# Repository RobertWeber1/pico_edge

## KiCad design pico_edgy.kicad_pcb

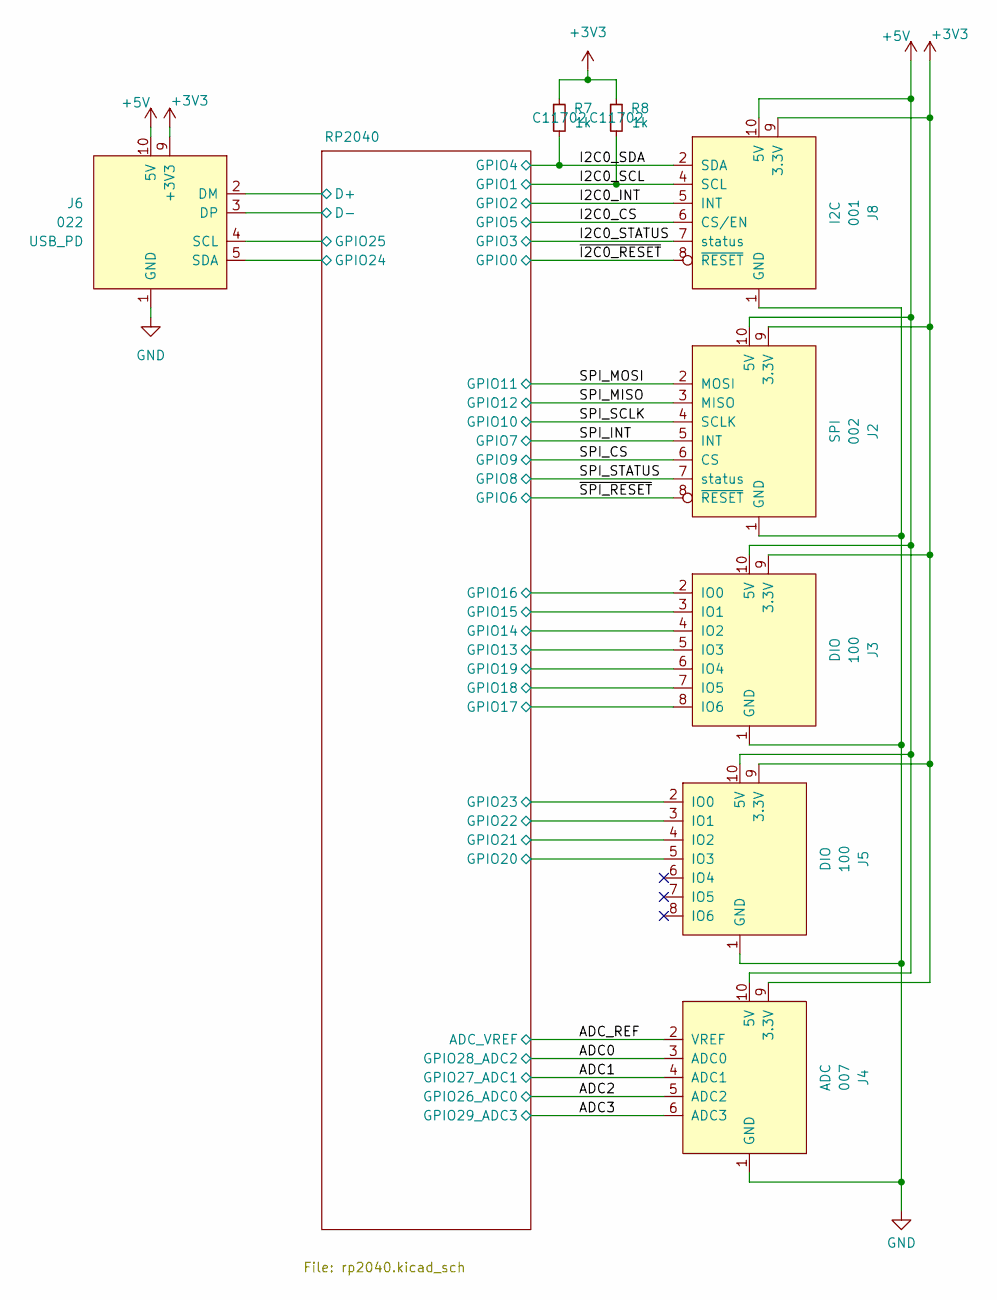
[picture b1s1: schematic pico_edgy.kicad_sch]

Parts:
J2: 002; on_edge_2x05_host
J3, J5: 100; on_edge_2x05_host
J4: 007; on_edge_2x05_host
J6: 022; on_edge_2x05_host
J8: 001; on_edge_2x05_host
R7, R8: 1k; R_0402_1005Metric; LCSC C25543

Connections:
+3V3: J2.9 (3.3V), J3.9 (3.3V), J4.9 (3.3V), J5.9 (3.3V), J6.9 (+3V3), J8.9 (3.3V), R7.1, R8.1; also elsewhere on the board
+5V: J2.10 (5V), J3.10 (5V), J4.10 (5V), J5.10 (5V), J6.10 (5V), J8.10 (5V)
/ADC0: J4.3 (ADC0); also elsewhere on the board
/ADC1: J4.4 (ADC1); also elsewhere on the board
/ADC2: J4.5 (ADC2); also elsewhere on the board
/ADC3: J4.6 (ADC3); also elsewhere on the board
/ADC_REF: J4.2 (VREF); also elsewhere on the board
/I2C0_CS: J8.6 (CS/EN); also elsewhere on the board
/I2C0_INT: J8.5 (INT); also elsewhere on the board
/I2C0_SCL: J8.4 (SCL), R8.2; also elsewhere on the board
/I2C0_SDA: J8.2 (SDA), R7.2; also elsewhere on the board
/I2C0_STATUS: J8.7 (status); also elsewhere on the board
/RP2040/D+: J6.2 (DM); also elsewhere on the board
/RP2040/D-: J6.3 (DP); also elsewhere on the board
/RP2040/GPIO13: J3.5 (IO3); also elsewhere on the board
/RP2040/GPIO14: J3.4 (IO2); also elsewhere on the board
/RP2040/GPIO15: J3.3 (IO1); also elsewhere on the board
/RP2040/GPIO16: J3.2 (IO0); also elsewhere on the board
/RP2040/GPIO17: J3.8 (IO6); also elsewhere on the board
/RP2040/GPIO18: J3.7 (IO5); also elsewhere on the board
/RP2040/GPIO19: J3.6 (IO4); also elsewhere on the board
/RP2040/GPIO20: J5.5 (IO3); also elsewhere on the board
/RP2040/GPIO21: J5.4 (IO2); also elsewhere on the board
/RP2040/GPIO22: J5.3 (IO1); also elsewhere on the board
/RP2040/GPIO23: J5.2 (IO0); also elsewhere on the board
/RP2040/GPIO24: J6.5 (SDA); also elsewhere on the board
/RP2040/GPIO25: J6.4 (SCL); also elsewhere on the board
/SPI_CS: J2.6 (CS); also elsewhere on the board
/SPI_INT: J2.5 (INT); also elsewhere on the board
/SPI_MISO: J2.3 (MISO); also elsewhere on the board
/SPI_MOSI: J2.2 (MOSI); also elsewhere on the board
/SPI_SCLK: J2.4 (SCLK); also elsewhere on the board
/SPI_STATUS: J2.7 (status); also elsewhere on the board
/~I2C0_RESET: J8.8 (~RESET); also elsewhere on the board
/~SPI_RESET: J2.8 (~RESET); also elsewhere on the board
GND: J2.1 (GND), J3.1 (GND), J4.1 (GND), J5.1 (GND), J6.1 (GND), J8.1 (GND); also elsewhere on the board

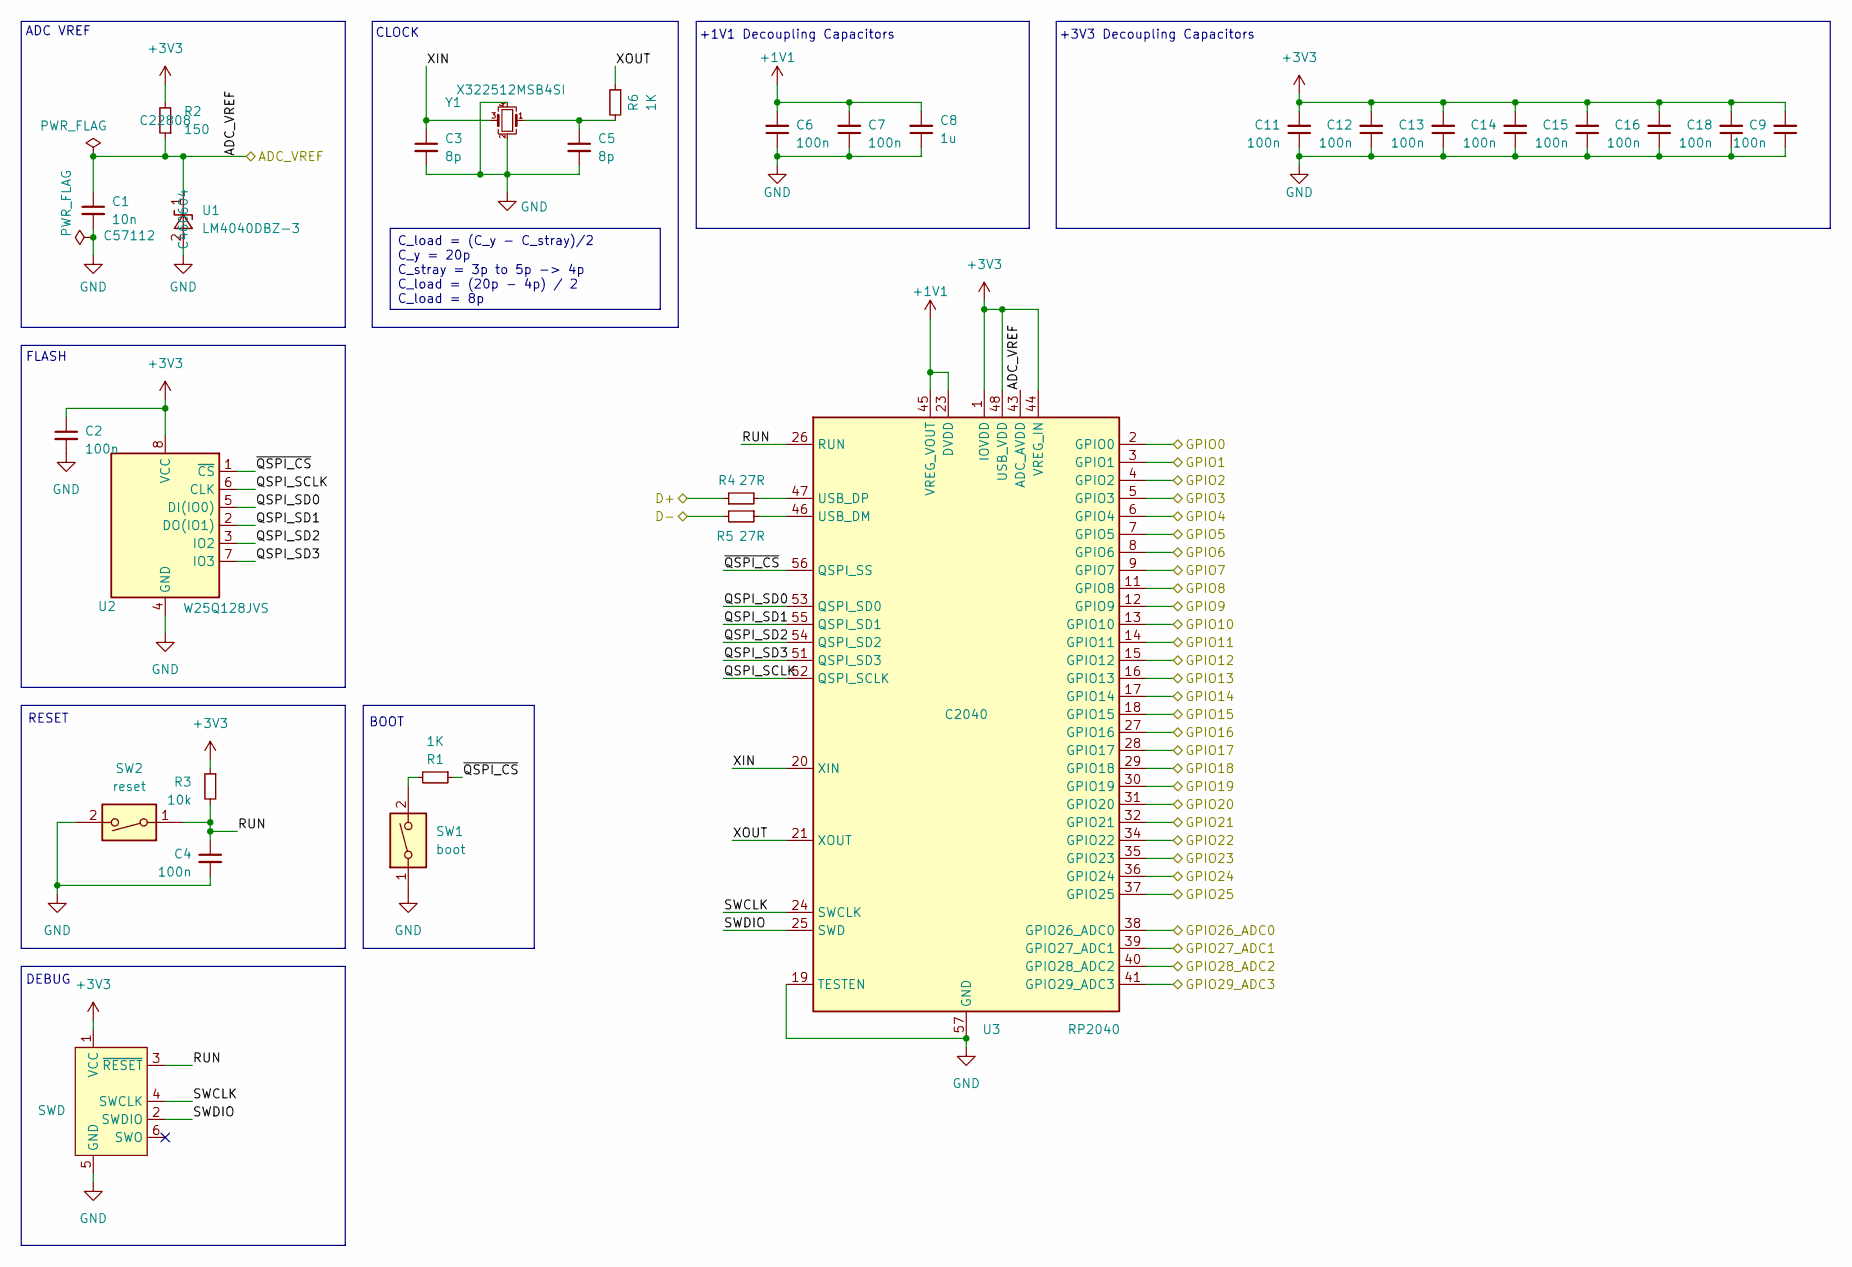
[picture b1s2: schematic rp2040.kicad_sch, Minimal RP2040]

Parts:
C1: 10n; C_0603_1608Metric_Pad1.08x0.95mm_HandSolder; LCSC C76599
C2, C4, C6, C7, C9, C11, C12, C13, C14, C15, C16, C18: 100n; C_0402_1005Metric_Pad0.74x0.62mm_HandSolder; LCSC Part# C307331
C3, C5: 8p; C_0402_1005Metric_Pad0.74x0.62mm_HandSolder; LCSC Part# C130118
C8: 1u; C_0402_1005Metric_Pad0.74x0.62mm_HandSolder; LCSC Part# C52923
J1: SWD; Tag-Connect_TC2030-IDC-NL_2x03_P1.27mm_Vertical
R1, R6: 1K; R_0402_1005Metric_Pad0.72x0.64mm_HandSolder; LCSC Part# C11702
R2: 150; R_0603_1608Metric_Pad0.98x0.95mm_HandSolder; LCSC C22808
R3: 10k; R_0402_1005Metric_Pad0.72x0.64mm_HandSolder; LCSC Part# C25744
R4, R5: 27R; R_0402_1005Metric_Pad0.72x0.64mm_HandSolder; LCSC Part# C140174
SW1: boot; SW_Push_1P1T_XKB_TS-1187A; LCSC Part# C318884
SW2: reset; SW_Push_1P1T_XKB_TS-1187A; LCSC Part# C318884
U1: LM4040DBZ-3; SOT-23; LCSC C460726
U2: W25Q128JVS; WSON-8-1EP_6x5mm_P1.27mm_EP3.4x4.3mm; LCSC Part# C190862
U3: RP2040; QFN-56-1EP_7x7mm_P0.4mm_EP3.2x3.2mm; LCSC Part# C2040
Y1: X322512MSB4SI; Crystal_SMD_3225-4Pin_3.2x2.5mm; LCSC Part# C9002

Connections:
+1V1: C6.2, C7.2, C8.2, U3.23 (DVDD), U3.45 (VREG_VOUT), U3.50 (DVDD)
+3V3: C2.1, C9.2, C11.2, C12.2, C13.2, C14.2, C15.2, C16.2, C18.2, J1.1 (VCC), R2.2, R3.1, U2.8 (VCC), U3.1 (IOVDD), U3.10 (IOVDD), U3.22 (IOVDD), U3.33 (IOVDD), U3.42 (IOVDD), U3.44 (VREG_IN), U3.48 (USB_VDD), U3.49 (IOVDD); also elsewhere on the board
/ADC0: U3.40 (GPIO28_ADC2); also elsewhere on the board
/ADC1: U3.39 (GPIO27_ADC1); also elsewhere on the board
/ADC2: U3.38 (GPIO26_ADC0); also elsewhere on the board
/ADC3: U3.41 (GPIO29_ADC3); also elsewhere on the board
/ADC_REF: C1.1, R2.1, U1.1 (K), U3.43 (ADC_AVDD); also elsewhere on the board
/I2C0_CS: U3.7 (GPIO5); also elsewhere on the board
/I2C0_INT: U3.4 (GPIO2); also elsewhere on the board
/I2C0_SCL: U3.3 (GPIO1); also elsewhere on the board
/I2C0_SDA: U3.6 (GPIO4); also elsewhere on the board
/I2C0_STATUS: U3.5 (GPIO3); also elsewhere on the board
/RP2040/D+: R4.1; also elsewhere on the board
/RP2040/D-: R5.2; also elsewhere on the board
/RP2040/GPIO13: U3.16 (GPIO13); also elsewhere on the board
/RP2040/GPIO14: U3.17 (GPIO14); also elsewhere on the board
/RP2040/GPIO15: U3.18 (GPIO15); also elsewhere on the board
/RP2040/GPIO16: U3.27 (GPIO16); also elsewhere on the board
/RP2040/GPIO17: U3.28 (GPIO17); also elsewhere on the board
/RP2040/GPIO18: U3.29 (GPIO18); also elsewhere on the board
/RP2040/GPIO19: U3.30 (GPIO19); also elsewhere on the board
/RP2040/GPIO20: U3.31 (GPIO20); also elsewhere on the board
/RP2040/GPIO21: U3.32 (GPIO21); also elsewhere on the board
/RP2040/GPIO22: U3.34 (GPIO22); also elsewhere on the board
/RP2040/GPIO23: U3.35 (GPIO23); also elsewhere on the board
/RP2040/GPIO24: U3.36 (GPIO24); also elsewhere on the board
/RP2040/GPIO25: U3.37 (GPIO25); also elsewhere on the board
/RP2040/QSPI_SCLK: U2.6 (CLK), U3.52 (QSPI_SCLK)
/RP2040/QSPI_SD0: U2.5 (DI(IO0)), U3.53 (QSPI_SD0)
/RP2040/QSPI_SD1: U2.2 (DO(IO1)), U3.55 (QSPI_SD1)
/RP2040/QSPI_SD2: U2.3 (IO2), U3.54 (QSPI_SD2)
/RP2040/QSPI_SD3: U2.7 (IO3), U3.51 (QSPI_SD3)
/RP2040/RUN: C4.1, J1.3 (~RESET), R3.2, SW2.1, U3.26 (RUN)
/RP2040/SWCLK: J1.4 (SWCLK), U3.24 (SWCLK)
/RP2040/SWDIO: J1.2 (SWDIO), U3.25 (SWD)
/RP2040/XIN: C3.1, U3.20 (XIN), Y1.3
/RP2040/XOUT: R6.1, U3.21 (XOUT)
/RP2040/~QSPI_CS: R1.1, U2.1 (~CS), U3.56 (QSPI_SS)
/SPI_CS: U3.12 (GPIO9); also elsewhere on the board
/SPI_INT: U3.9 (GPIO7); also elsewhere on the board
/SPI_MISO: U3.15 (GPIO12); also elsewhere on the board
/SPI_MOSI: U3.14 (GPIO11); also elsewhere on the board
/SPI_SCLK: U3.13 (GPIO10); also elsewhere on the board
/SPI_STATUS: U3.11 (GPIO8); also elsewhere on the board
/~I2C0_RESET: U3.2 (GPIO0); also elsewhere on the board
/~SPI_RESET: U3.8 (GPIO6); also elsewhere on the board
GND: C1.2, C2.2, C3.2, C4.2, C5.2, C6.1, C7.1, C8.1, C9.1, C11.1, C12.1, C13.1, C14.1, C15.1, C16.1, C18.1, J1.5 (GND), SW1.1, SW2.2, U1.2 (A), U2.4 (GND), U3.19 (TESTEN), U3.57 (GND), Y1.2, Y1.4; also elsewhere on the board
unnamed: C5.1, R6.2, Y1.1
unnamed: R1.2, SW1.2
unnamed: R5.1, U3.46 (USB_DM)
unnamed: R4.2, U3.47 (USB_DP)

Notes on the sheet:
FLASH
DEBUG
BOOT
RESET
CLOCK
+3V3 Decoupling Capacitors
ADC VREF
+1V1 Decoupling Capacitors
C_load = (C_y - C_stray)/2 C_y = 20p C_stray = 3p to 5p -> 4p C_load = (20p - 4p) / 2 C_load = 8p

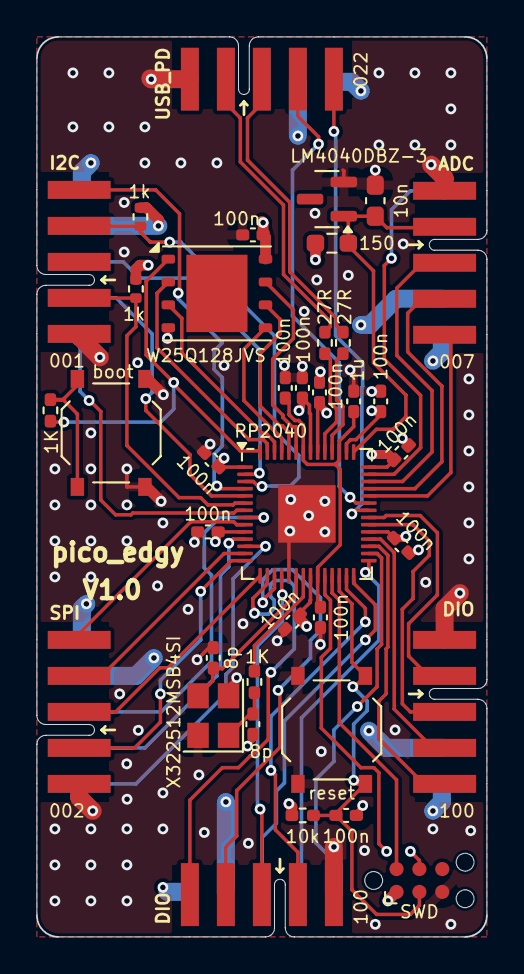
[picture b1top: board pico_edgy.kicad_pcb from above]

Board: 4 copper layers, 25.0 x 50.0 mm, 37 parts (0 on the bottom side), 52 nets.

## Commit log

2024-10-18 Add put_on_edge submodule
2024-10-20 WIP: layout from scratch
2024-10-25 layout from scratch, change some components to basic JLCPCB parts
